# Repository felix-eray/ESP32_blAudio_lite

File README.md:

# ESP32_blAudio_lite
Hello Simos. I chose this path because I did not know how to contact you. "https://forum.esk8.news/t/general-diy-audio-project-thread/14032/10" I could not reach the DSP project made with STA309A in the project mentioned in this link. If you don't mind, I would appreciate it if you could share the project on github. Sorry for causing you inconvenience. Thanks.

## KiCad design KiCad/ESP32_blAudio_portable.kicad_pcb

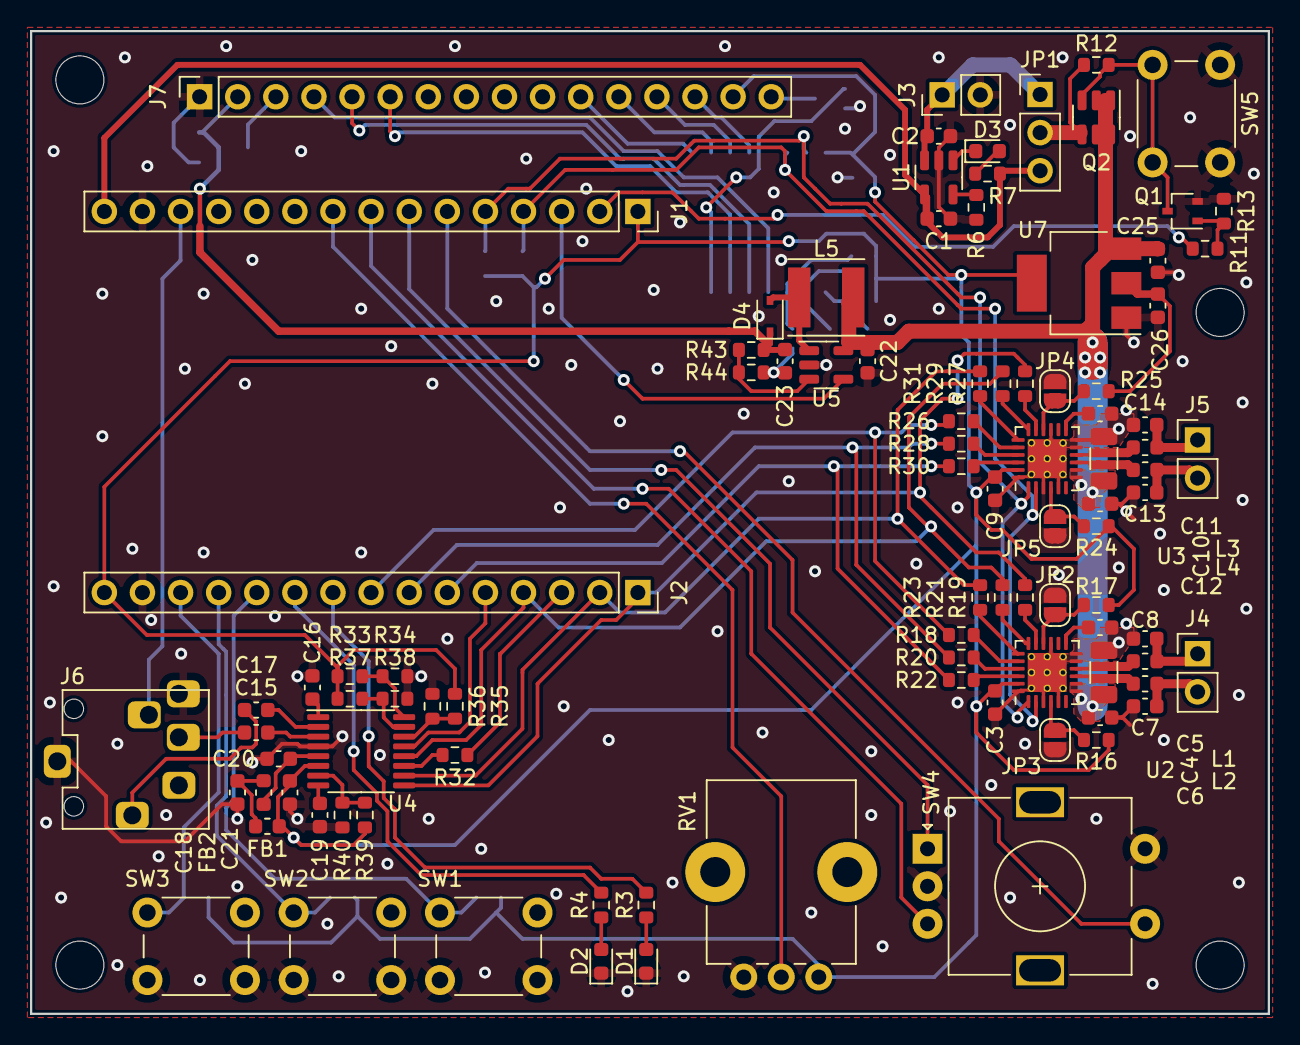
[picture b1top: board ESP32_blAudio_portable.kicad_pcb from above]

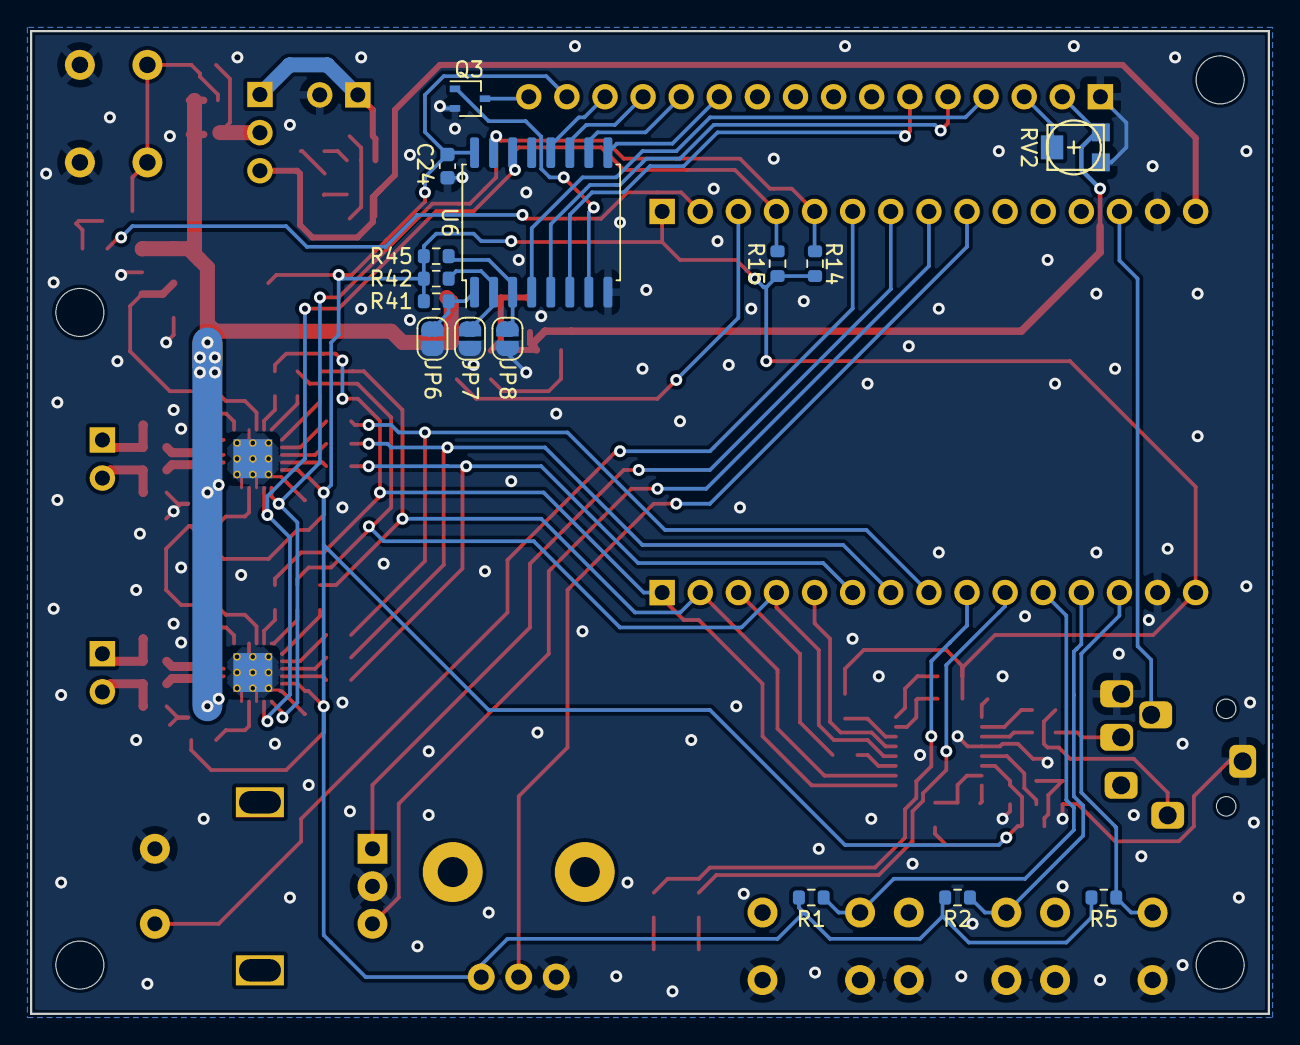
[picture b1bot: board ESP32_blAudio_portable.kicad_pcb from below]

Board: 2 copper layers, 82.5 x 65.5 mm, 111 parts (15 on the bottom side), 90 nets.

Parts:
C1, C2, C22, C23, C24, C25, C26: 1u; C_0603_1608Metric
C3, C5, C6, C7, C8, C9, C11, C12, C13, C14: 100n; C_0603_1608Metric
C4, C10: 22u; C_1206_3216Metric
C15, C17: 10µ; C_0603_1608Metric
C16, C18, C19, C21: 1µ; C_0603_1608Metric
C20: 220n; C_0603_1608Metric
D1, D2, D3: LED; LED_0603_1608Metric
D4: 30V 1A; D_SOD-323
FB1, FB2: 600R; L_0603_1608Metric
J1, J2: Conn_01x15_Male; PinSocket_1x15_P2.54mm_Vertical
J3, J4, J5: Conn_01x02_Male; PinHeader_1x02_P2.54mm_Vertical
J6: ASJ-99H
J7: Conn_01x16_Female; PinSocket_1x16_P2.54mm_Vertical
JP1: Jumper_3_Open; PinHeader_1x03_P2.54mm_Vertical
JP2, JP3, JP4, JP5: SJ; SolderJumper-2_P1.3mm_Open_RoundedPad1.0x1.5mm
JP6, JP7, JP8: SolderJumper_2_Open; SolderJumper-2_P1.3mm_Open_RoundedPad1.0x1.5mm
L1, L2, L3, L4: L; L_0603_1608Metric
L5: 33u; L_Taiyo-Yuden_NR-50xx
Q1, Q3: 2N7002; SOT-323_SC-70
Q2: Q_PMOS_DGS; SOT-23-6
R1, R2, R5, R6, R7, R12, R13, R14, R15, R43, R44: 10k; R_0603_1608Metric
R3, R4: 120R; R_0603_1608Metric
R11: 100R; R_0603_1608Metric
R16, R17, R24, R25, R41, R42, R45: 110k; R_0603_1608Metric
R18, R19, R20, R21, R22, R23, R26, R27, R28, R29, R30, R31: 22R; R_0603_1608Metric
R32, R33, R34, R35, R36, R37, R38, R39, R40: R; R_0603_1608Metric
RV1: PT01; Potentiometer_Bourns_PTV09A-1_Single_Vertical
RV2: TC33X_10k; trimmer_Bourns_tc33x
SW1, SW2, SW3, SW5: TS02; SW_PUSH_6mm_H5mm
SW4: PEC12R; RotaryEncoder_Alps_EC11E-Switch_Vertical_H20mm
U1: MCP73831-2-OT; SOT-23-5
U2, U3: TFA9879HN; HVQFN-24-1EP_4x4mm_P0.5mm_EP2.6x2.6mm_ThermalVias
U4: AK5720VT; TSSOP-16_4.4x5mm_P0.65mm
U5: AP3012; SOT-23-5
U6: PCF8574; SOIC-16W_7.5x10.3mm_P1.27mm
U7: NCP1117-3.3_SOT223; SOT-223-3_TabPin2

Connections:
+3V3: C3.1, C9.1, C21.2, C24.1, C26.1, FB1.2, J1.1, J2.15, J7.15, R1.2, R2.2, R5.2, R14.1, R15.1, R16.1, R17.1, R24.1, R25.1, R33.1, R35.1, R37.1, R39.1, R41.2, R42.2, R45.2, RV1.1, U2.23 (VDD), U3.23 (VDD), U4.6 (VD), U6.16 (VDD), U7.2 (VO)
+5C: C23.1, D4.1 (K), J7.2, R43.2, RV2.3
+5V: C1.1, J1.15, JP1.3 (B), R7.2, U1.4 (VDD)
+BATT: C2.1, J3.1, JP1.1 (A), U1.3 (VBAT)
+VDC: C4.1, C6.1, C10.1, C12.1, C22.1, C25.1, L5.1, Q2.1 (D), U2.7 (VDDP), U2.8 (VDDP), U3.7 (VDDP), U3.8 (VDDP), U5.5 (IN), U7.3 (VI)
/3-5_SW: J1.13, J6.4
/ANA_VOL: J1.9, RV1.2
/BTTN1: J2.11, R1.1, SW1.2
/BTTN2: J2.12, R2.1, SW2.2
/BTTN3: J2.13, R5.1, SW3.2
/Display/LCD_BCKL_EN: Q3.1 (G), U6.7 (P3)
/Display/LCD_D4: J7.11, U6.9 (P4)
/Display/LCD_D5: J7.12, U6.10 (P5)
/Display/LCD_D6: J7.13, U6.11 (P6)
/Display/LCD_D7: J7.14, U6.12 (P7)
/Display/LCD_E: J7.6, U6.6 (P2)
/Display/LCD_RS: J7.4, U6.4 (P0)
/Display/LCD_R/~W: J7.5, U6.5 (P1)
/ENC_A: J1.7, SW4.A
/ENC_B: J1.8, SW4.B
/ENC_SW: J1.6, SW4.S1
/EN_5V: J1.3, U5.4 (~SHDN)
/LED1: J2.9, R3.2
/LED2: J2.10, R4.2
/LRCK1: J2.6, R22.1, R30.1
/LRCK2: J2.2, R23.1, R31.1, U4.10 (LRCLK)
/MCLK: J2.3, R32.2
/PWR_ON: J1.2, R11.1
/SCK1: J2.7, R20.1, R28.1
/SCK2: J2.4, R21.1, R29.1, U4.12 (BICK)
/SCL: J1.4, R15.2, U2.2 (SCL), U3.2 (SCL), U6.14 (SCL)
/SDA: J1.5, R14.2, U2.1 (SDA), U3.1 (SDA), U6.15 (SDA)
/SDI1: J2.8, R18.1, R26.1
/SDI2: J2.1, R19.1, R27.1, U4.9 (SDTO)
/~PDN: J2.5, U4.13 (~PDN)
GND: C1.2, C2.2, C3.2, C4.2, C5.2, C6.2, C7.2, C8.2, C9.2, C10.2, C11.2, C12.2, C13.2, C14.2, C16.2, C18.1, C19.2, C20.1, C21.1, C22.2, C23.2, C24.2, C25.2, C26.2, D1.1 (K), D2.1 (K), J1.14, J2.14, J3.2, J6.5, J6.S, J7.1, JP2.1 (A), JP3.1 (A), JP4.1 (A), JP5.1 (A), JP6.1 (A), JP7.1 (A), JP8.1 (A), Q1.2 (S), Q3.2 (S), R6.1, R13.2, R34.2, R36.2, R38.2, R40.2, R44.1, RV1.3, RV2.1, SW1.1, SW2.1, SW3.1, SW4.C, SW4.S2, SW5.1, U1.2 (VSS), U2.3 (TEST1), U2.5 (TEST3), U2.11 (GNDP), U2.12 (GNDP), U2.15 (TEST2), U2.24 (GNDD), U2.25 (EP), U3.3 (TEST1), U3.5 (TEST3), U3.11 (GNDP), U3.12 (GNDP), U3.15 (TEST2), U3.24 (GNDD), U3.25 (EP), U4.4 (VSS), U5.2 (GND), U6.8 (VSS), U7.1 (GND)
unnamed: C5.1, U2.13 (STABA)
unnamed: C7.1, J4.2, L2.2
unnamed: C8.1, J4.1, L1.2
unnamed: C11.1, U3.13 (STABA)
unnamed: C13.1, J5.2, L4.2
unnamed: C14.1, J5.1, L3.2
unnamed: C15.1, U4.3 (LIN)
unnamed: C15.2, J6.T
unnamed: C16.1, U4.1 (VCOM)
unnamed: C17.1, U4.2 (RIN)
unnamed: C17.2, J6.R
unnamed: C18.2, FB1.1, FB2.2
unnamed: C19.1, U4.8 (REGO)
unnamed: C20.2, FB2.1, U4.5 (VA)
unnamed: D1.2 (A), R3.1
unnamed: D2.2 (A), R4.1
unnamed: D3.1 (K), U1.1 (STAT)
unnamed: D3.2 (A), R7.1
unnamed: D4.2 (A), L5.2, U5.1 (SW)
unnamed: J7.3, RV2.2
unnamed: J7.16, Q3.3 (D)
unnamed: JP1.2 (C), Q2.3 (S), R12.1
unnamed: JP2.2 (B), R17.2, U2.16 (ADSEL1)
unnamed: JP3.2 (B), R16.2, U2.4 (ADSEL2)
unnamed: JP4.2 (B), R25.2, U3.16 (ADSEL1)
unnamed: JP5.2 (B), R24.2, U3.4 (ADSEL2)
unnamed: JP6.2 (B), R41.1, U6.1 (A0)
unnamed: JP7.2 (B), R42.1, U6.2 (A1)
unnamed: JP8.2 (B), R45.1, U6.3 (A2)
unnamed: L1.1, U2.10 (OUTA)
unnamed: L2.1, U2.9 (OUTB)
unnamed: L3.1, U3.10 (OUTA)
unnamed: L4.1, U3.9 (OUTB)
unnamed: Q1.1 (G), R11.2, R13.1
unnamed: Q1.3 (D), Q2.2 (G), R12.2, SW5.2
unnamed: R6.2, U1.5 (PROG)
unnamed: R18.2, U2.20 (SDI1)
unnamed: R19.2, U2.17 (SDI2)
unnamed: R20.2, U2.21 (SCK1)
unnamed: R21.2, U2.18 (SCK2)
unnamed: R22.2, U2.22 (LRCK1)
unnamed: R23.2, U2.19 (LRCK2)
unnamed: R26.2, U3.20 (SDI1)
unnamed: R27.2, U3.17 (SDI2)
unnamed: R28.2, U3.21 (SCK1)
unnamed: R29.2, U3.18 (SCK2)
unnamed: R30.2, U3.22 (LRCK1)
unnamed: R31.2, U3.19 (LRCK2)
unnamed: R32.1, U4.11 (MCLK)
unnamed: R33.2, R34.1, U4.16 (CKS)
unnamed: R35.2, R36.1, U4.14 (DIF/TDMI)
unnamed: R37.2, R38.1, U4.15 (FSEL)
unnamed: R39.2, R40.1, U4.7 (GSEL)
unnamed: R43.1, R44.2, U5.3 (FB)

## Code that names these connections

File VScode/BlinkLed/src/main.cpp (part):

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const int pwrEN = 12;
const int en5V = 13;
const int sw3_5mm = 35;
const int LRCK1 = 19;
const int LRCK2 = 22;
const int BCLK1 = 18;
const int BCLK2 = 3;
const int SDI1 = 5;
const int SDI2 = 23;
const int MCLK = 1;

//TFA9879, I2C-address 0b11011YX, solder bridge open = 1, closed = 0, (JP4/JP2) = X, (JP5/JP3) = Y
//both open: 0b1101111
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
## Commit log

2022-09-30 -initial commit
2022-09-30 -associated footprints to more specific components -added manufacturer and part series info to more specific components
2022-09-30 -layout work
2022-10-02 -layout largely finished, some finishing touches needed
2022-10-02 -fixed .gitignore for the kicad's project backup files
2022-10-03 -First board version ready to order
2022-10-16 -boards on hand atm, assembling first board and finalizing used component values
2022-10-16 -More HW updates and corrections -basic FW
2022-10-17 -updated schematic component values, updated schematic PDF -added simple bass and treble control for the TF9879 amp
2022-10-20 -added treble and bass control function and added some delay to power-up sequence to hopefully fix weird power-on issue with ADC or amp, which causes this weird bump thumping on power-up
2022-10-20 -started working on library for the TFA9879 amp, for easier use
2022-10-22 -Been developing the TFA9879 control library -added volume control for the analog potentiometer in the main loop
2022-10-23 -added bluetooth audio library to platformio.ini folder -basic bluetooth audio functionality also operational -added parametric EQ configuration TFA9879 library
2022-10-23 -added pin out map for the ESP32 module -Long button 1 press now toggles between bluetooth and 3,5mm jack as audio sources
2022-10-24 -added shutdown board to long press of button 3
2022-10-24 -added potential library for driving the character LCD through the PCF8574 I2C-IO expander
2022-10-29 -LCD driver library through PCF8574A I2C-IO expander added
2022-10-29 -new branch for creating a custom hook into the A2DP sink bluetooth library
2022-10-30 -added LCD screen test code -rewrote the pushbutton reading function, so it works better with slower polling
2022-10-31 -fixed some variable related shenanigans in the button press function
